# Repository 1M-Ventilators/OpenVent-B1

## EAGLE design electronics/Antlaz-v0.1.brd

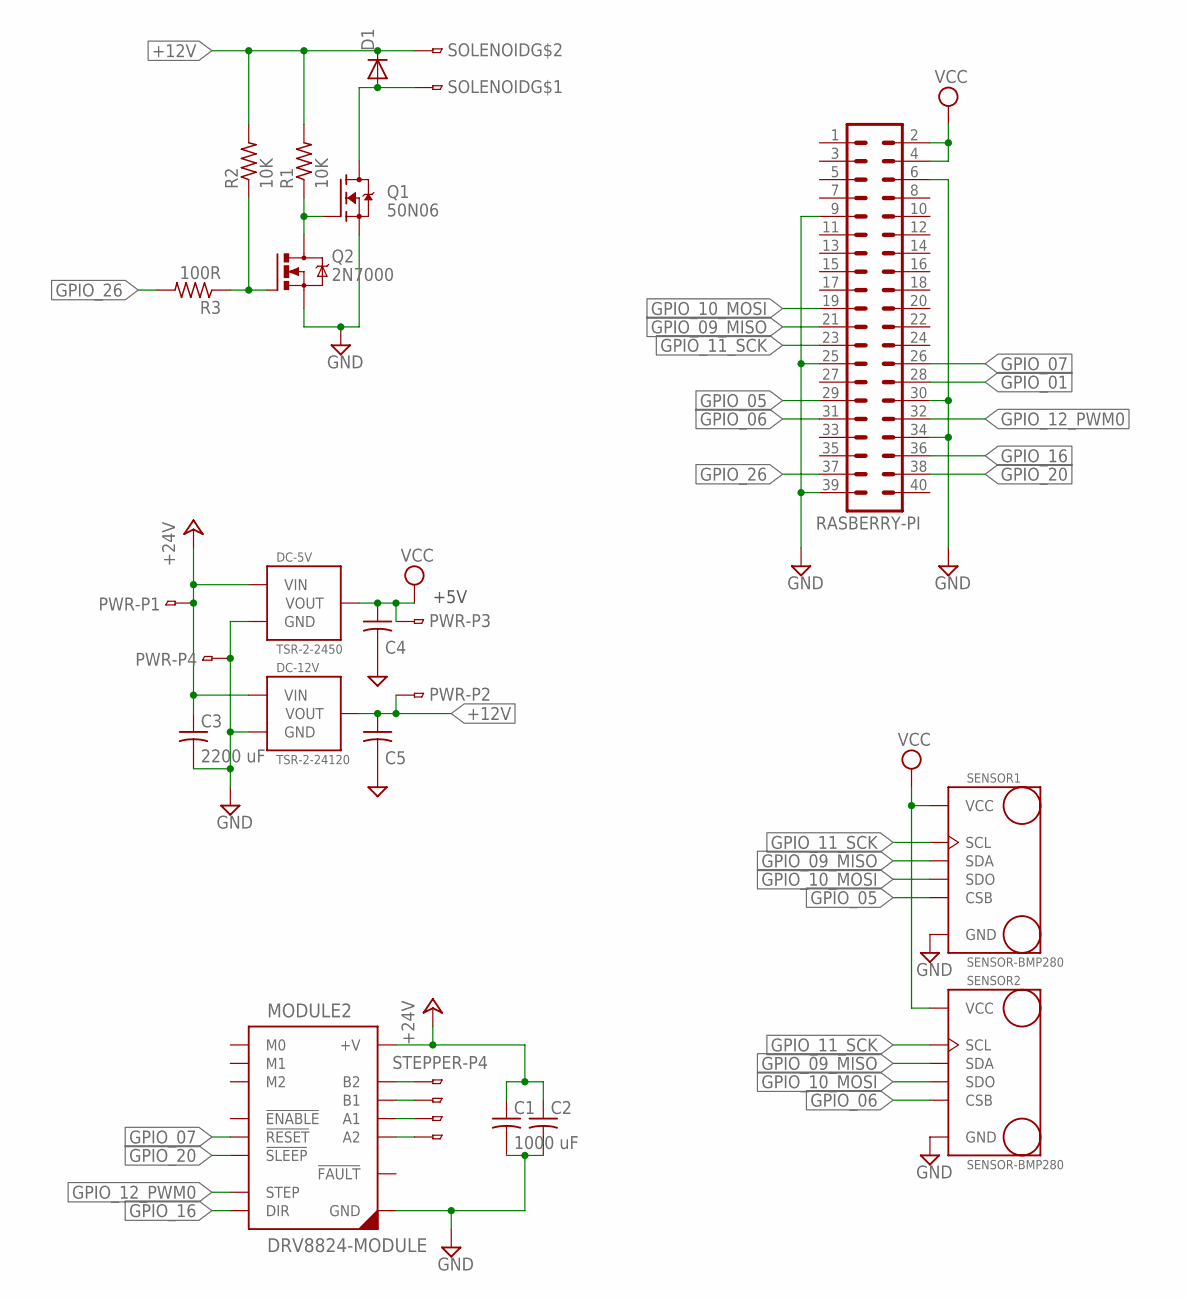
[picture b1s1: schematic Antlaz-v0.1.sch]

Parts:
C1: 1000 uF; CAP_18MM
C2, C4, C5: C-US_BYPASS; KEMET-CERMAIC
C3: 2200 uF; CAP_18MM
D1: DIODEDO07; DO07
DC-5V: TSR-2-2450; DCDC_TSR2
DC-12V: TSR-2-24120; DCDC_TSR2
MODULE2: DRV8824-MODULE; DRV8825
PWR: CONN-4; CONN-PHEONIX-3,5MM-4
Q1: 50N06; TO220
Q2: 2N7000; TO92
R1, R2: 10K; 0207/10
R3: 100R; 0207/10
RASBERRY-PI: MA20-2
SENSOR1, SENSOR2: SENSOR-BMP280; MA06-1
SOLENOID: CONN-2; CONN-PHEONIX-3,5MM-2
STEPPER: CONN-4; CONN-PHEONIX-3,5MM-4

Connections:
+12V: C5.1, D1.C, DC-12V.P$3 (VOUT), PWR.P$2, R1.2, R2.2, SOLENOID.P$2
+24V: C1.1, C2.1, C3.1, DC-5V.P$1 (VIN), DC-12V.P$1 (VIN), MODULE2.P$16 (+V), PWR.P$1
GND: C1.2, C2.2, C3.2, C4.2, C5.2, DC-5V.P$2 (GND), DC-12V.P$2 (GND), MODULE2.P$9 (GND), MODULE2.P$15 (GND), PWR.P$4, Q1.3 (S), Q2.3 (S), RASBERRY-PI.6, RASBERRY-PI.9, RASBERRY-PI.25, RASBERRY-PI.30, RASBERRY-PI.34, RASBERRY-PI.39, SENSOR1.2 (GND), SENSOR2.2 (GND)
GPIO_01: RASBERRY-PI.28
GPIO_05: RASBERRY-PI.29, SENSOR1.5 (CSB)
GPIO_06: RASBERRY-PI.31, SENSOR2.5 (CSB)
GPIO_07: MODULE2.P$5 (!RESET), RASBERRY-PI.26
GPIO_09_MISO: RASBERRY-PI.21, SENSOR1.4 (SDA), SENSOR2.4 (SDA)
GPIO_10_MOSI: RASBERRY-PI.19, SENSOR1.6 (SDO), SENSOR2.6 (SDO)
GPIO_11_SCK: RASBERRY-PI.23, SENSOR1.3 (SCL), SENSOR2.3 (SCL)
GPIO_12_PWM0: MODULE2.P$7 (STEP), RASBERRY-PI.32
GPIO_16: MODULE2.P$8 (DIR), RASBERRY-PI.36
GPIO_20: MODULE2.P$6 (!SLEEP), RASBERRY-PI.38
GPIO_26: R3.2, RASBERRY-PI.37
unnamed: Q2.2 (G), R2.1, R3.1
unnamed: MODULE2.P$14 (B2), STEPPER.P$4
unnamed: MODULE2.P$13 (B1), STEPPER.P$3
unnamed: MODULE2.P$12 (A1), STEPPER.P$2
unnamed: MODULE2.P$11 (A2), STEPPER.P$1
unnamed: D1.A, Q1.2 (D), SOLENOID.P$1
unnamed: Q1.1 (G), Q2.1 (D), R1.1
VCC: C4.1, DC-5V.P$3 (VOUT), PWR.P$3, RASBERRY-PI.2, RASBERRY-PI.4, SENSOR1.1 (VCC), SENSOR2.1 (VCC)

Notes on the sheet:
+5V

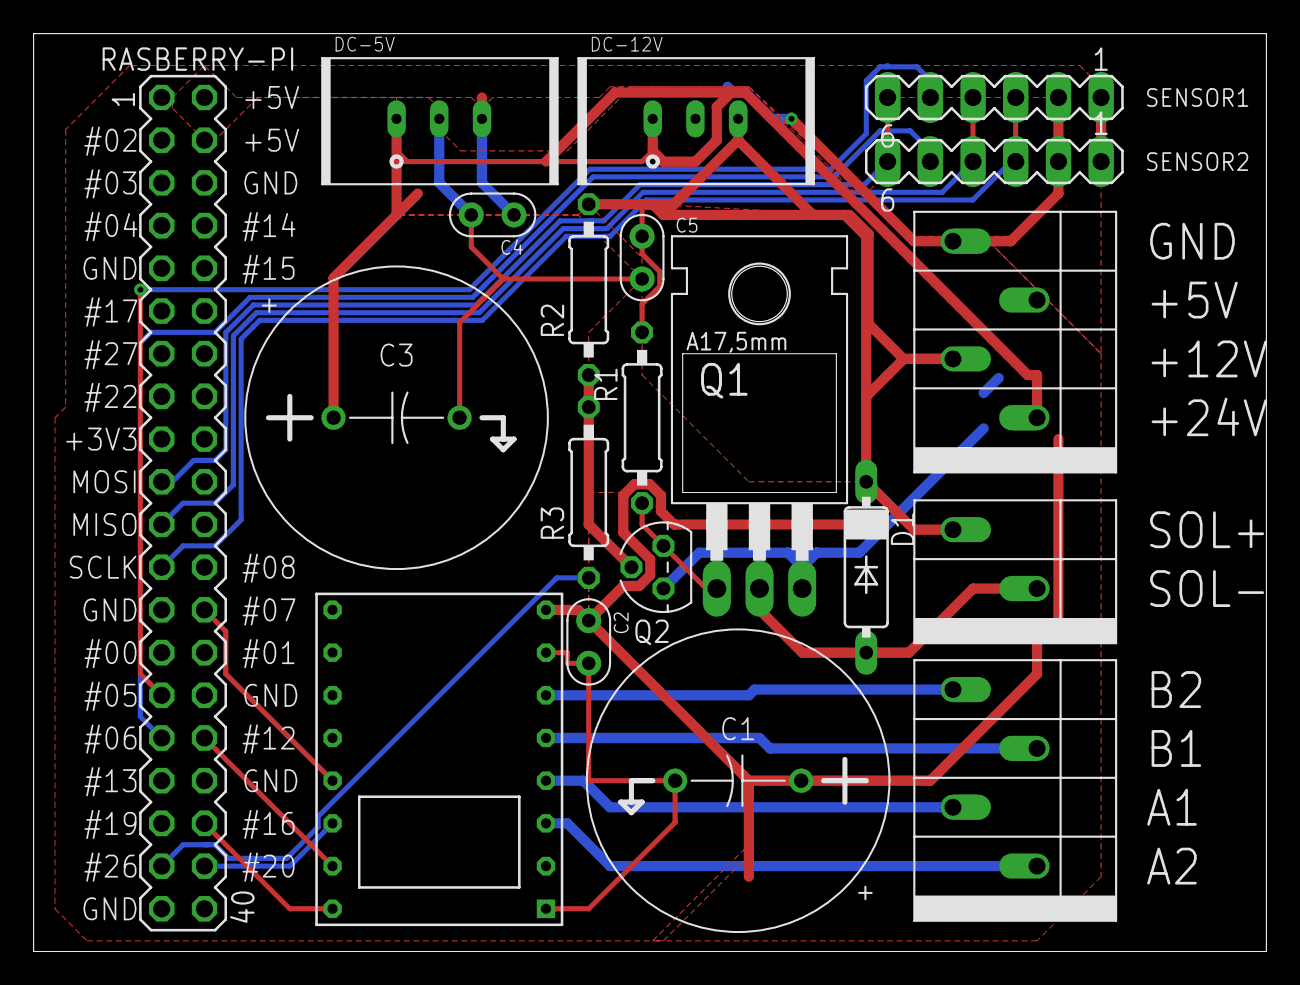
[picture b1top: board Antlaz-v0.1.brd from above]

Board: 2 copper layers, 73.3 x 54.6 mm, 20 parts (0 on the bottom side), 21 nets.

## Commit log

2020-04-06 push @antalz's changes
2020-04-09 Redesigning piston pump
    Redesign of the piston pump to get a sturdier mount, and the have a better parametric design that allows for different lengths and diameters of tubing
2020-04-09 Moving file to CAD subsolder
2020-04-17 Adding board+schematic and system overview
2020-04-22 code refactor, moved constants to settings file
2020-04-22 cleanup
2020-04-24 CAD work done
2020-05-24 Overview images to go along with google drive docs
